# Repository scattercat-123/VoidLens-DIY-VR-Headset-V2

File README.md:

# VoidLens DIY VR Headset

## Project Overview

## Schematic and Connection Diagram

## Hardware Details & Assembly

## What makes this special?
 - A highly customizable VR Headset
 - Custom PCB
 - Aesthetic design
 - Low power consumption
 - DP/HDMI Cable directly to the pc or laptop
 - Accurate IMU's and rf modules

## How to make this?
Firstly, the pcb gerber files are in the pcb folder inside the main repo, it must be exactly printed and parts can be choosen according to you by following the BOM(bom.csv).
Next, Each part in the prints folder must be printed and then assembled according to the main .step file(more coming soon)

https://github.com/HadesVR/HadesVR - All the source codes are availble in this repo and many other repos.

The pcb has a 6 pin programmer to flash the code into the atmega32u4. Additionally, a usb c is provided if a bootloader is loaded on the mcu one can directly flash to it.

A Mini DP port coming out of the dual screens display driver(Check BOM) is connected to the host pc)
SteamVR can be installed on the pc and the documentation is availble here - https://github.com/HadesVR/HadesVR

## Credits:
https://github.com/HadesVR/HadesVR - HadesVR Inspired me to make this in the first place
Thanks for the horizons team for organizing horizons europa which gave me the motivation to finish this.

I have also used a bit of ai(google's search engine) and some claude to help me finish the BOM file faster instead of doing manually and help me understand some pcb design concepts.

*sorry this readme isnt properly maintained, will update soon*

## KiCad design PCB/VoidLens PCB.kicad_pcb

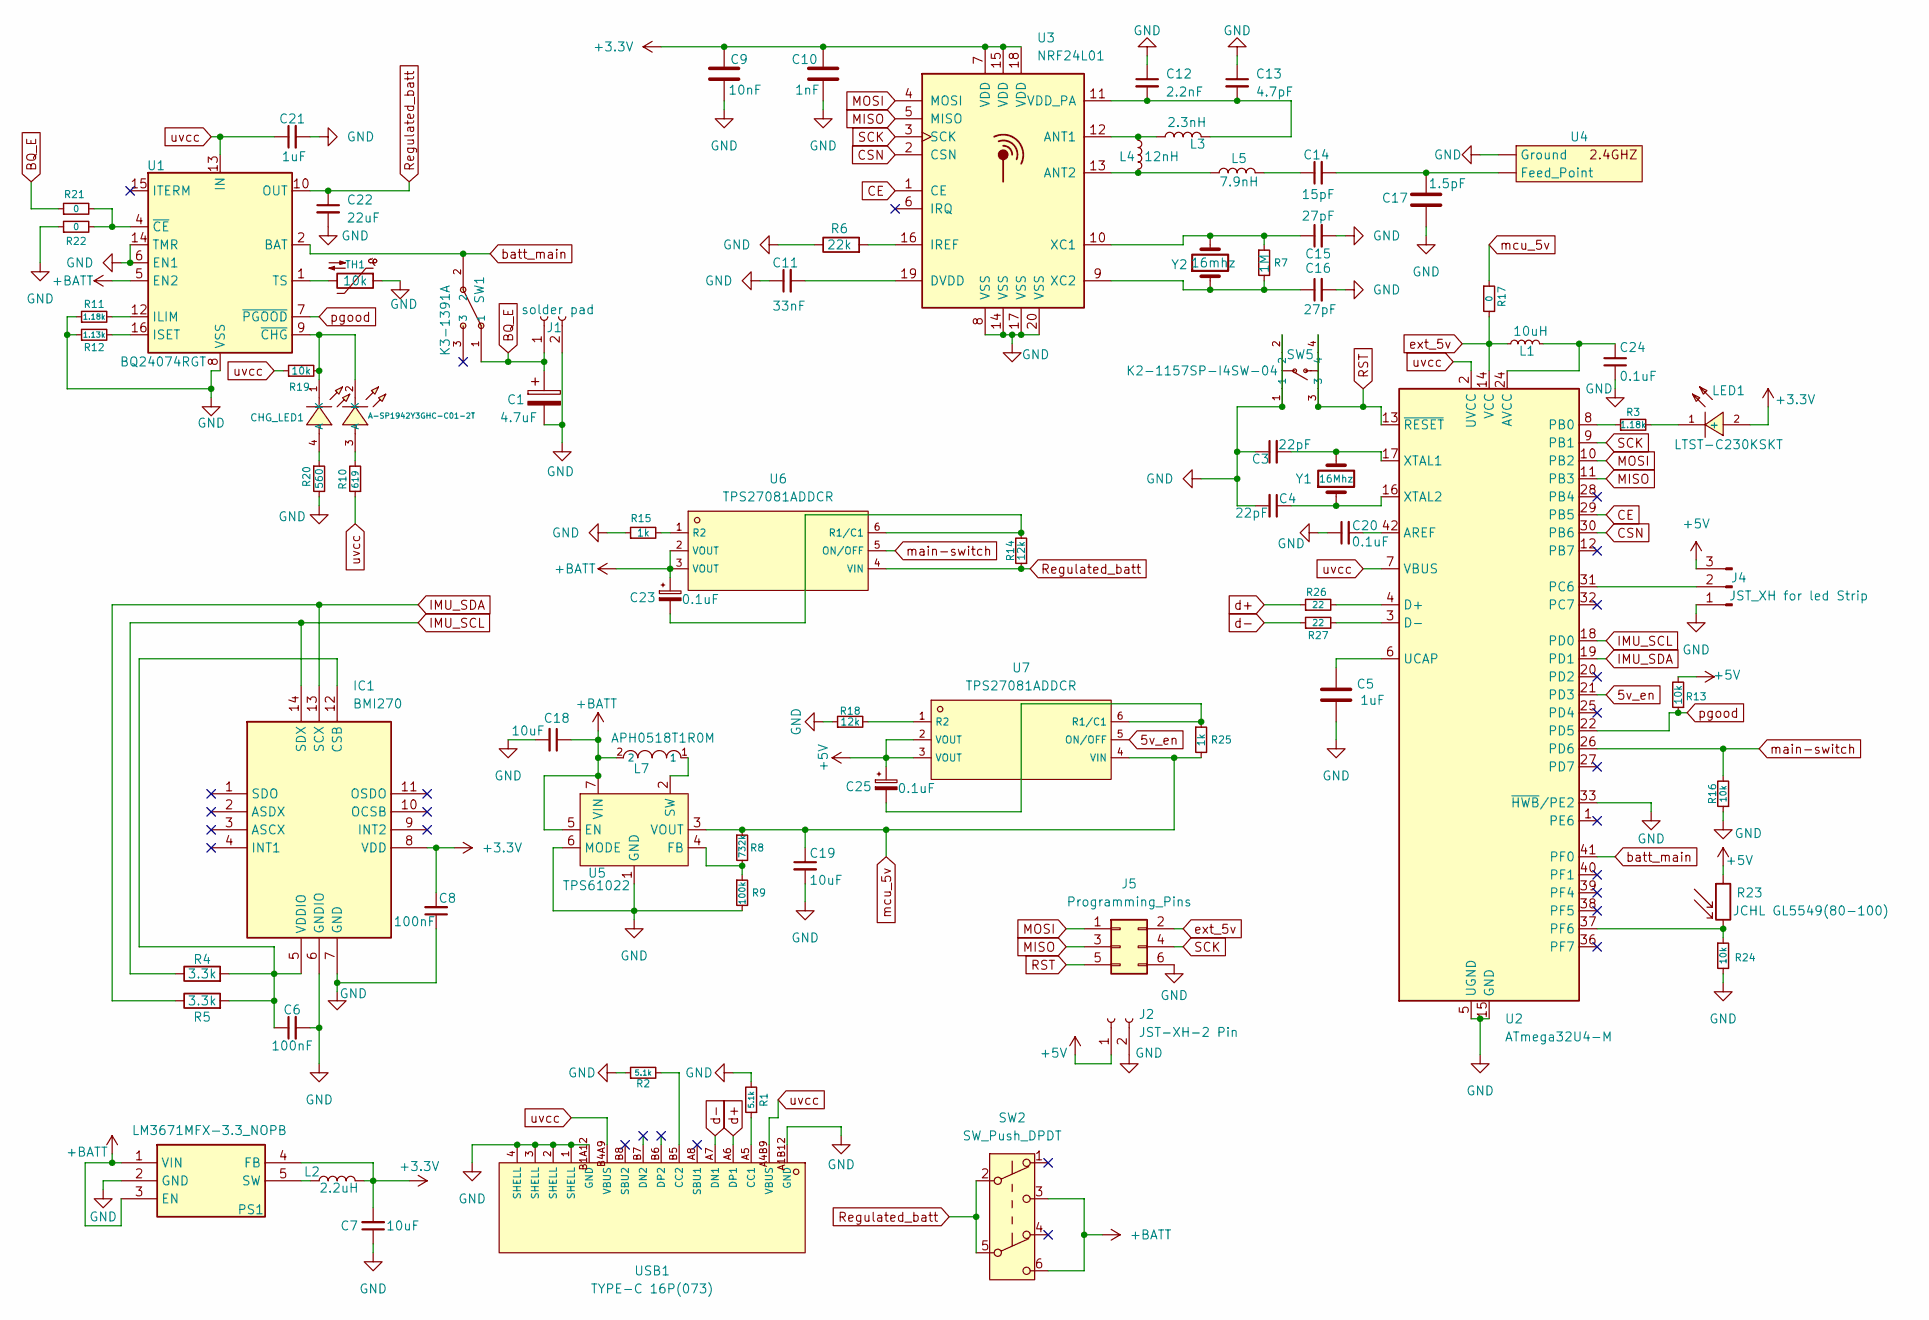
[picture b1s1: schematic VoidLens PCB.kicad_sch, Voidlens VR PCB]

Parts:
C1: 4.7uF; CP_Elec_4x5.4
C3, C4: 22pF; C_0603_1608Metric_Pad1.08x0.95mm_HandSolder
C5, C21: 1uF; C_0603_1608Metric_Pad1.08x0.95mm_HandSolder
C6, C8: 100nF; C_0603_1608Metric_Pad1.08x0.95mm_HandSolder
C7, C18, C19: 10uF; C_0603_1608Metric_Pad1.08x0.95mm_HandSolder
C9: 10nF; C_0603_1608Metric_Pad1.08x0.95mm_HandSolder
C10: 1nF; C_0603_1608Metric_Pad1.08x0.95mm_HandSolder
C11: 33nF; C_0603_1608Metric_Pad1.08x0.95mm_HandSolder
C12: 2.2nF; C_0603_1608Metric_Pad1.08x0.95mm_HandSolder
C13: 4.7pF; C_0603_1608Metric_Pad1.08x0.95mm_HandSolder
C14: 15pF; C_0603_1608Metric_Pad1.08x0.95mm_HandSolder
C15, C16: 27pF; C_0603_1608Metric_Pad1.08x0.95mm_HandSolder
C17: 1.5pF; C_0603_1608Metric_Pad1.08x0.95mm_HandSolder
C20, C23, C24, C25: 0.1uF; C_0603_1608Metric_Pad1.08x0.95mm_HandSolder
C22: 22uF; CP_Elec_4x5.4
CHG_LED1: A-SP1942Y3GHC-C01-2T; C19171267_LED-SMD_4P-L1_6-W1_5_A-SP1942Y3GHC-C01-2T; LCSC C19171267
IC1: BMI270; Bosch_LGA-14_3x2.5mm_P0.5mm; Manufacturer_Part_Number BMI270; Mouser Part Number 262-BMI270
J1: solder pad; 01x02 Solder Pad 3mm Dia, 2mm Spacing
J2: JST-XH-2 Pin; JST_XH_B2B-XH-A_1x02_P2.50mm_Vertical
J4: JST_XH for led Strip; JST_XH_B3B-XH-A_1x03_P2.50mm_Vertical
J5: Programming_Pins; PinHeader_2x03_P2.54mm_Vertical
L1: 10uH; L_0805_2012Metric_Pad1.05x1.20mm_HandSolder
L2: 2.2uH; L_1008_2520Metric_Pad1.43x2.20mm_HandSolder
L3: 2.3nH; L_0201_0603Metric_Pad0.64x0.40mm_HandSolder
L4: 12nH; L_0402_1005Metric_Pad0.77x0.64mm_HandSolder
L5: 7.9nH; L_0402_1005Metric_Pad0.77x0.64mm_HandSolder
L7: APH0518T1R0M; C5349672_IND-SMD_L5_4-W5_2; LCSC C5349672
LED1: LTST-C230KSKT; C125108_LED1206-RD_YELLOW-SIDE; LCSC C125108
PS1: LM3671MFX-3.3_NOPB; SOT-23-5_HandSoldering; Manufacturer_Part_Number LM3671MFX-3.3/NOPB; Mouser Part Number 926-LM3671MFX33NOPB
R1, R2: 5.1k; R_0603_1608Metric_Pad0.98x0.95mm_HandSolder
R3, R11: 1.18k; R_0603_1608Metric_Pad0.98x0.95mm_HandSolder
R4, R5: 3.3k; R_0603_1608Metric_Pad0.98x0.95mm_HandSolder
R6: 22k; R_0603_1608Metric_Pad0.98x0.95mm_HandSolder
R7: 1M; R_0603_1608Metric_Pad0.98x0.95mm_HandSolder
R8: 732k; R_0603_1608Metric_Pad0.98x0.95mm_HandSolder
R9: 100k; R_0603_1608Metric_Pad0.98x0.95mm_HandSolder
R10: 619; R_0603_1608Metric_Pad0.98x0.95mm_HandSolder
R12: 1.13k; R_0603_1608Metric_Pad0.98x0.95mm_HandSolder
R13, R16, R19, R24: 10k; R_0603_1608Metric_Pad0.98x0.95mm_HandSolder
R14, R18: 12k; R_0603_1608Metric_Pad0.98x0.95mm_HandSolder
R15, R25: 1k; R_0603_1608Metric_Pad0.98x0.95mm_HandSolder
R17, R21, R22: 0; R_0603_1608Metric_Pad0.98x0.95mm_HandSolder
R20: 560; R_0603_1608Metric_Pad0.98x0.95mm_HandSolder
R23: JCHL GL5549(80-100); R_LDR_4.9x4.2mm_P2.54mm_Vertical
R26, R27: 22; R_0603_1608Metric_Pad0.98x0.95mm_HandSolder
SW1: K3-1391A; C92655_SW-TH_K3-1391A; LCSC C92655
SW2: SW_Push_DPDT; SW-TH_6P-L5.8-W5.8-P2.00-LS4.5-BL
SW5: K2-1157SP-I4SW-04; C2909692_SW-SMD_4P-L6_2-W6_2-P4_50-LS8_6; LCSC C2909692
TH1: 10k; R_Axial_DIN0204_L3.6mm_D1.6mm_P5.08mm_Horizontal
U1: BQ24074RGT; VQFN-16-1EP_3x3mm_P0.5mm_EP1.6x1.6mm
U2: ATmega32U4-M; QFN-44-1EP_7x7mm_P0.5mm_EP5.2x5.2mm
U3: NRF24L01; QFN-20-1EP_4x4mm_P0.5mm_EP2.5x2.5mm
U4: 2.4Ghz PCB Antenna
U5: TPS61022; Texas_RWU0007A_VQFN-7_2x2mm_P0.5mm
U6, U7: TPS27081ADDCR; C128404_SOT-23-6_L2_9-W1_6-P0_95-LS2_8-BR; LCSC C128404
USB1: TYPE-C 16P(073); C668624_USB-C-SMD_TYPE-C16PIN_C668624; LCSC C668624
Y1: 16Mhz; Crystal_HC49-4H_Vertical
Y2: 16mhz; Crystal_HC49-4H_Vertical

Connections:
5v_en: U2.21 (PD3), U7.5 (ON/OFF)
+3.3V: C7.2, C8.2, C9.1, C10.1, IC1.8 (VDD), L2.2, LED1.2 (+), PS1.4 (FB), U3.7 (VDD), U3.15 (VDD), U3.18 (VDD)
+5V: C25.1, J2.1, J4.3, R13.2, R23.1, U7.2 (VOUT), U7.3 (VOUT)
+BATT: C18.1, C23.1, L7.2, PS1.1 (VIN), PS1.3 (EN), SW2.3 (C), SW2.6 (C), U1.5 (EN2), U5.5 (EN), U5.7 (VIN), U6.2 (VOUT), U6.3 (VOUT)
BQ_E: C1.1, J1.1, R21.1, SW1.1
CE: U2.29 (PB5), U3.1 (CE)
CSN: U2.30 (PB6), U3.2 (CSN)
GND: C1.2, C3.1, C4.2, C5.2, C6.2, C7.1, C8.1, C9.2, C10.2, C11.1, C12.1, C13.1, C15.2, C16.2, C17.2, C18.2, C19.2, C20.1, C21.2, C22.2, C24.2, IC1.6 (GNDIO), IC1.7 (GND), J1.2, J2.2, J4.1, J5.6, PS1.2 (GND), R1.2, R2.1, R6.1, R9.2, R11.1, R12.1, R15.1, R16.1, R18.1, R20.2, R22.1, R24.2, SW5.1, SW5.2, TH1.1, U1.6 (EN1), U1.8 (VSS), U1.14 (TMR), U1.17 (VSS), U2.5 (UGND), U2.15 (GND), U2.23 (GND), U2.33 (~HWB/PE2), U2.35 (GND), U2.43 (GND), U2.45 (GND), U3.8 (VSS), U3.14 (VSS), U3.17 (VSS), U3.20 (VSS), U3.21, U4., U4.1, U5.1 (GND), U5.6 (MODE), USB1.1 (SHELL), USB1.2 (SHELL), USB1.3 (SHELL), USB1.4 (SHELL), USB1.A1B12 (GND), USB1.B1A12 (GND)
IMU_SCL: IC1.14 (SDX), R4.1, U2.18 (PD0)
IMU_SDA: IC1.13 (SCX), R5.1, U2.19 (PD1)
MISO: J5.3, U2.11 (PB3), U3.5 (MISO)
MOSI: J5.1, U2.10 (PB2), U3.4 (MOSI)
unnamed: C14.1, L5.2
unnamed: C24.1, L1.2, U2.24 (AVCC), U2.44 (AVCC)
unnamed: CHG_LED1.3 (A), R10.2
unnamed: CHG_LED1.4 (A), R20.1
unnamed: C6.1, IC1.5 (VDDIO), IC1.12 (CSB), R4.2, R5.2
unnamed: J4.2, U2.31 (PC6)
unnamed: LED1.1 (-), R3.2
unnamed: L2.1, PS1.5 (SW)
unnamed: R11.2, U1.12 (ILIM)
unnamed: R12.2, U1.16 (ISET)
unnamed: TH1.2, U1.1 (TS)
unnamed: R21.2, R22.2, U1.4 (~CE)
unnamed: CHG_LED1.1 (K), CHG_LED1.2 (K), R19.2, U1.9 (~CHG)
unnamed: C20.2, U2.42 (AREF)
unnamed: R26.2, U2.4 (D+)
unnamed: R27.2, U2.3 (D-)
unnamed: R3.1, U2.8 (PB0)
unnamed: R23.2, R24.1, U2.37 (PF6)
unnamed: C5.1, U2.6 (UCAP)
unnamed: C3.2, U2.17 (XTAL1), Y1.2
unnamed: C4.1, U2.16 (XTAL2), Y1.1
unnamed: L3.1, L4.1, U3.12 (ANT1)
unnamed: L4.2, L5.1, U3.13 (ANT2), U4.2
unnamed: C11.2, U3.19 (DVDD)
unnamed: R6.2, U3.16 (IREF)
unnamed: C12.2, C13.2, L3.2, U3.11 (VDD_PA)
unnamed: C15.1, R7.1, U3.10 (XC1), Y2.2
unnamed: C16.1, R7.2, U3.9 (XC2), Y2.1
unnamed: C14.2, C17.1, U4.
unnamed: R8.2, R9.1, U5.4 (FB)
unnamed: L7.1, U5.2 (SW)
unnamed: C23.2, R14.2, U6.6 (R1/C1)
unnamed: R15.2, U6.1 (R2)
unnamed: C25.2, R25.1, U7.6 (R1/C1)
unnamed: R18.2, U7.1 (R2)
unnamed: R1.1, USB1.A5 (CC1)
unnamed: R2.2, USB1.B5 (CC2)
RST: J5.5, SW5.3, SW5.4, U2.13 (~RESET)
Regulated_batt: C22.1, R14.1, SW2.2 (B), SW2.5 (B), U1.10 (OUT), U1.11 (OUT), U6.4 (VIN)
SCK: J5.4, U2.9 (PB1), U3.3 (SCK)
batt_main: SW1.2, U1.2 (BAT), U1.3 (BAT), U2.41 (PF0)
d+: R26.1, USB1.A6 (DP1)
d-: R27.1, USB1.A7 (DN1)
ext_5v: J5.2, L1.1, R17.2, U2.14 (VCC), U2.34 (VCC)
main-switch: R16.2, U2.26 (PD6), U6.5 (ON/OFF)
mcu_5v: C19.1, R8.1, R17.1, R25.2, U5.3 (VOUT), U7.4 (VIN)
pgood: R13.1, U1.7 (~PGOOD), U2.22 (PD5)
uvcc: C21.1, R10.1, R19.1, U1.13 (IN), U2.2 (UVCC), U2.7 (VBUS), USB1.A4B9 (VBUS), USB1.B4A9 (VBUS)

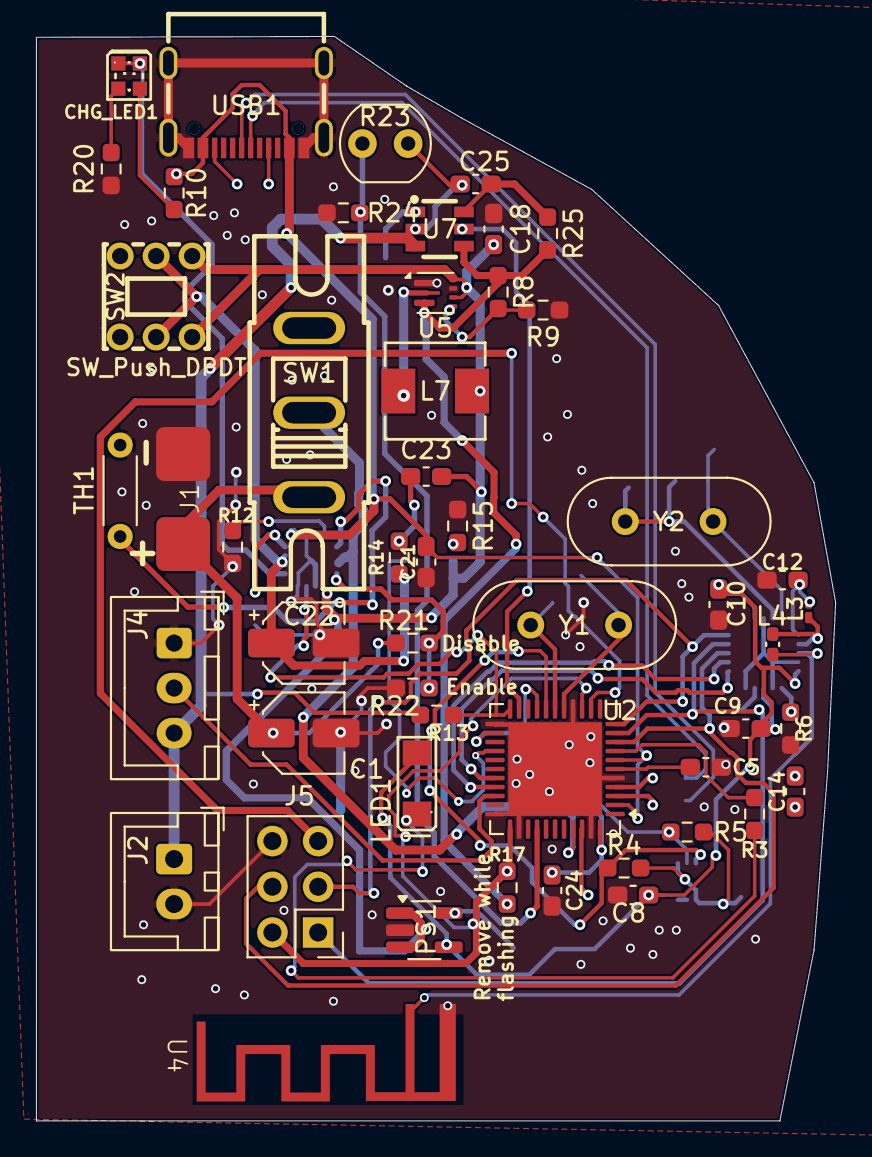
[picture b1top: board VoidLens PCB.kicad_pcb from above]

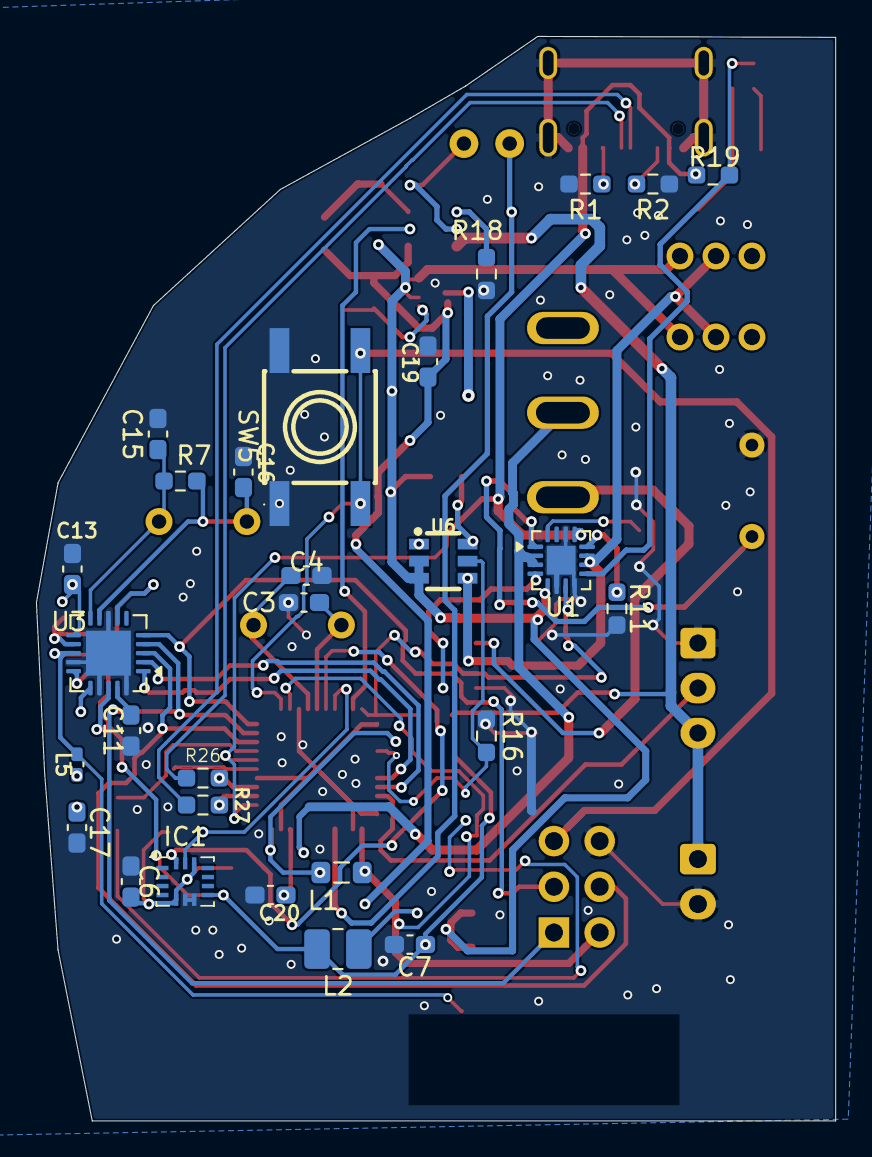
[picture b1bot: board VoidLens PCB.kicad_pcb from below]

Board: 2 copper layers, 44.4 x 60.2 mm, 79 parts (28 on the bottom side), 60 nets.
